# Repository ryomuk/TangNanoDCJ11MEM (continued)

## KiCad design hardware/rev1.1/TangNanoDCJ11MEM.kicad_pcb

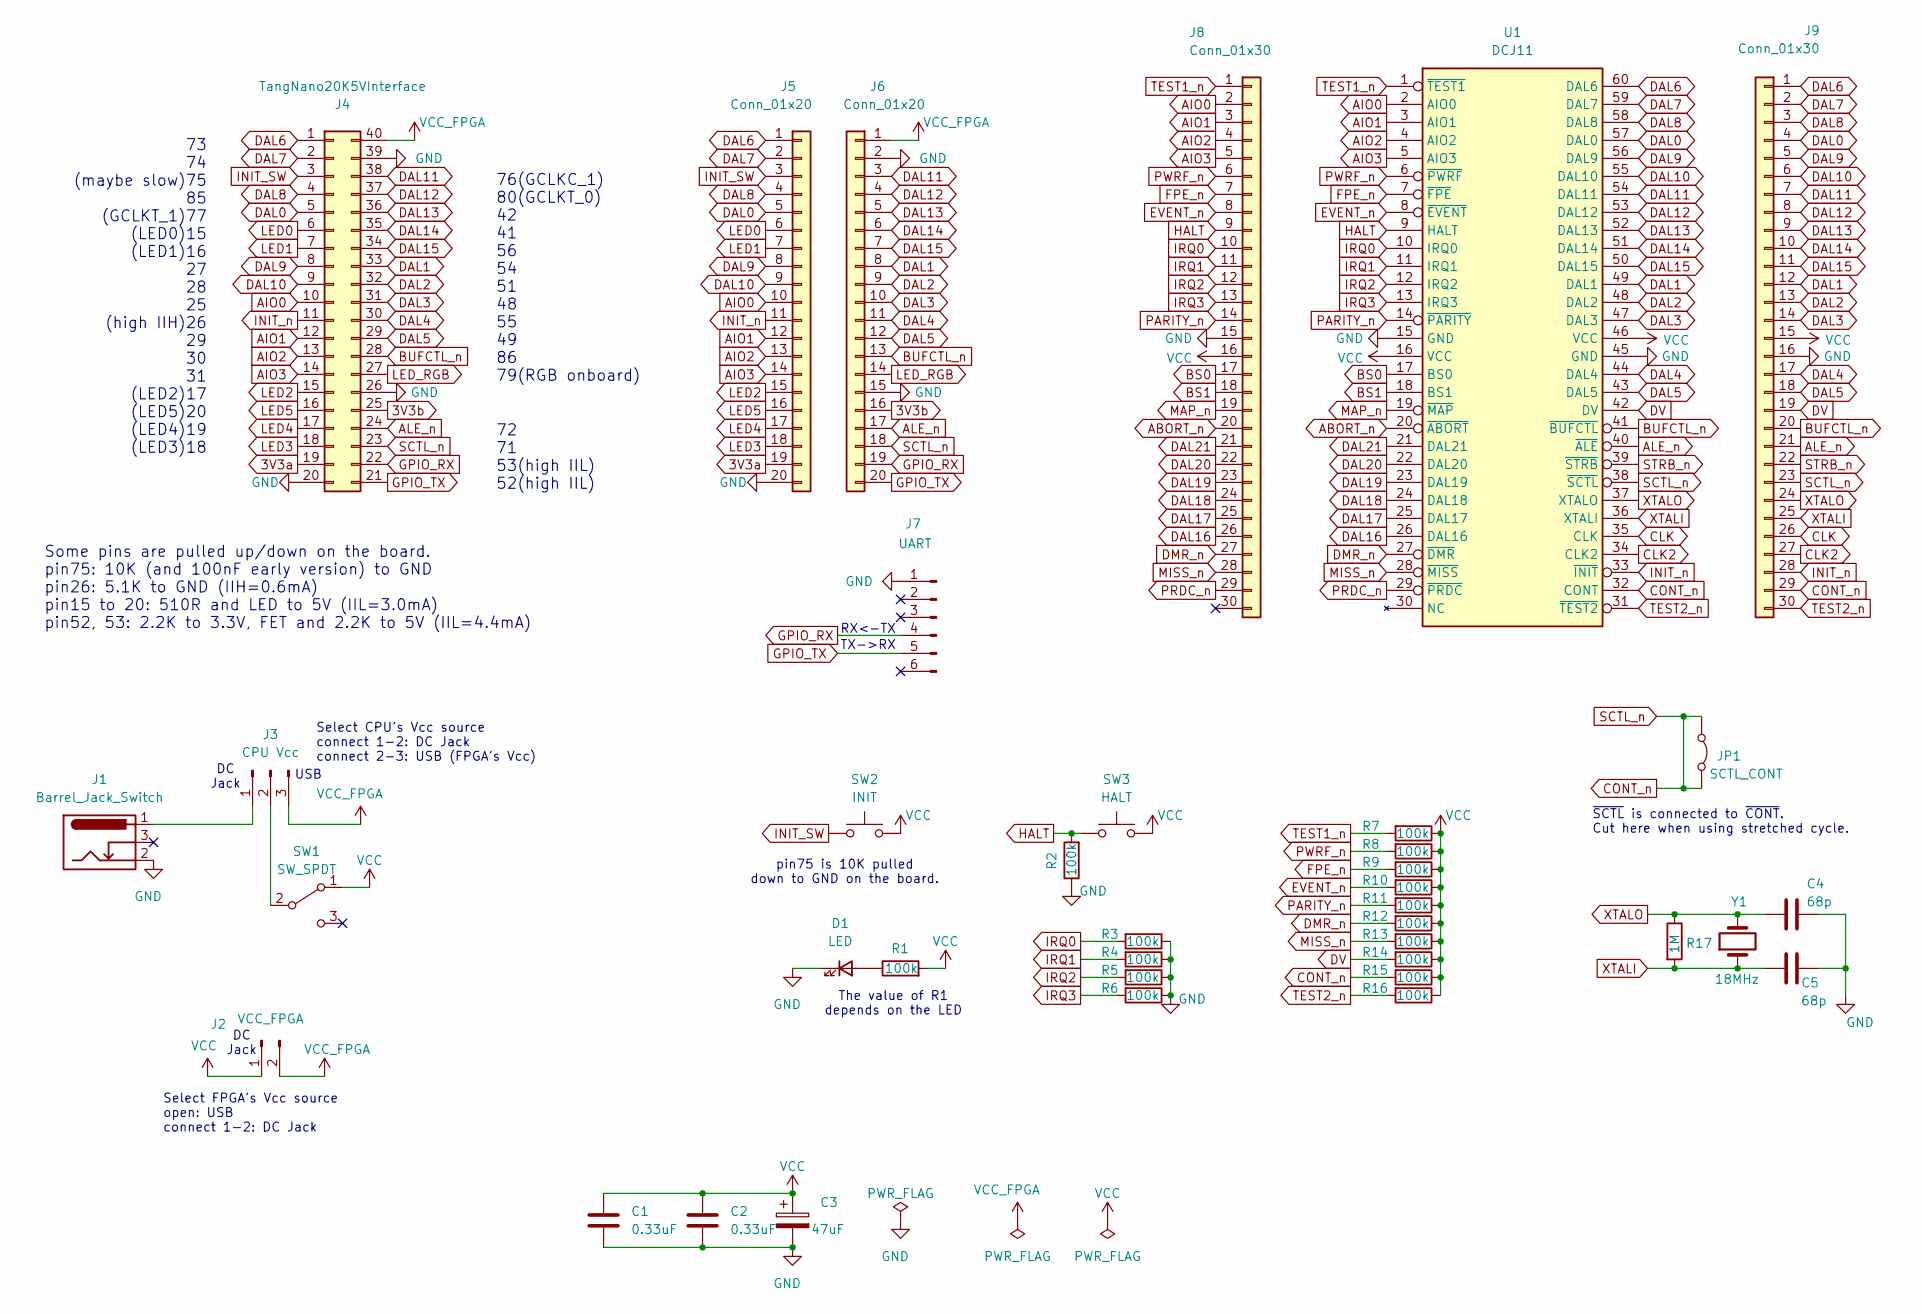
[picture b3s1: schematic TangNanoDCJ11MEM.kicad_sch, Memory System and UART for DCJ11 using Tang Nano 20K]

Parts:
C1, C2: 0.33uF; C_Disc_D5.0mm_W2.5mm_P2.50mm
C3: 47uF; CP_Radial_D6.3mm_P2.50mm
C4, C5: 68p; C_Disc_D5.0mm_W2.5mm_P2.50mm
D1: LED; LED_D3.0mm
J1: Barrel_Jack_Switch; BarrelJack_Horizontal
J2: VCC_FPGA; PinHeader_1x02_P2.54mm_Vertical
J3: CPU Vcc; PinHeader_1x03_P2.54mm_Vertical
J4: TangNano20K5VInterface; DIP-40_W15.24mm_Socket
J5, J6: Conn_01x20; PinSocket_1x20_P2.54mm_Vertical
J7: UART; PinHeader_1x06_P2.54mm_Horizontal
J8, J9: Conn_01x30; PinSocket_1x30_P2.54mm_Vertical
JP1: SCTL_CONT; JumperedPinHeader_1x02_P2.54mm_Vertical
R1, R2, R3, R4, R5, R6, R7, R8, R9, R10, R11, R12, R13, R14, R15, R16: 100k; R_Axial_DIN0207_L6.3mm_D2.5mm_P7.62mm_Horizontal
R17: 1M; R_Axial_DIN0207_L6.3mm_D2.5mm_P7.62mm_Horizontal
SW1: SW_SPDT; SW_SPDT_Toggle_with_mount
SW2: INIT; SW_PUSH_6mm_H4.3mm
SW3: HALT; SW_PUSH_6mm_H4.3mm
U1: DCJ11; DIP-60_W33.02mm_LongPads
Y1: 18MHz; Crystal_HC49-U_Vertical

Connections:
3V3a: J4.19, J5.19
3V3b: J4.25, J6.16
ABORT_n: J8.20, U1.20 (~ABORT)
AIO0: J4.10, J5.10, J8.2, U1.2 (AIO0)
AIO1: J4.12, J5.12, J8.3, U1.3 (AIO1)
AIO2: J4.13, J5.13, J8.4, U1.4 (AIO2)
AIO3: J4.14, J5.14, J8.5, U1.5 (AIO3)
ALE_n: J4.24, J6.17, J9.21, U1.40 (~ALE)
BS0: J8.17, U1.17 (BS0)
BS1: J8.18, U1.18 (BS1)
BUFCTL_n: J4.28, J6.13, J9.20, U1.41 (~BUFCTL)
CLK: J9.26, U1.35 (CLK)
CLK2: J9.27, U1.34 (CLK2)
CONT_n: J4.23, J6.18, J9.23, J9.29, JP1.1 (A), JP1.2 (B), R15.2, U1.32 (CONT), U1.38 (~SCTL)
DAL0: J4.5, J5.5, J9.4, U1.57 (DAL0)
DAL1: J4.33, J6.8, J9.12, U1.49 (DAL1)
DAL2: J4.32, J6.9, J9.13, U1.48 (DAL2)
DAL3: J4.31, J6.10, J9.14, U1.47 (DAL3)
DAL4: J4.30, J6.11, J9.17, U1.44 (DAL4)
DAL5: J4.29, J6.12, J9.18, U1.43 (DAL5)
DAL6: J4.1, J5.1, J9.1, U1.60 (DAL6)
DAL7: J4.2, J5.2, J9.2, U1.59 (DAL7)
DAL8: J4.4, J5.4, J9.3, U1.58 (DAL8)
DAL9: J4.8, J5.8, J9.5, U1.56 (DAL9)
DAL10: J4.9, J5.9, J9.6, U1.55 (DAL10)
DAL11: J4.38, J6.3, J9.7, U1.54 (DAL11)
DAL12: J4.37, J6.4, J9.8, U1.53 (DAL12)
DAL13: J4.36, J6.5, J9.9, U1.52 (DAL13)
DAL14: J4.35, J6.6, J9.10, U1.51 (DAL14)
DAL15: J4.34, J6.7, J9.11, U1.50 (DAL15)
DAL16: J8.26, U1.26 (DAL16)
DAL17: J8.25, U1.25 (DAL17)
DAL18: J8.24, U1.24 (DAL18)
DAL19: J8.23, U1.23 (DAL19)
DAL20: J8.22, U1.22 (DAL20)
DAL21: J8.21, U1.21 (DAL21)
DMR_n: J8.27, R12.2, U1.27 (~DMR)
DV: J9.19, R14.2, U1.42 (DV)
EVENT_n: J8.8, R10.2, U1.8 (~EVENT)
FPE_n: J8.7, R9.2, U1.7 (~FPE)
GND: C1.2, C2.2, C3.2, C4.1, C5.1, D1.1 (K), J1.2, J4.20, J4.26, J4.39, J5.20, J6.2, J6.15, J7.1, J8.15, J9.16, R2.1, R3.1, R4.1, R5.1, R6.1, U1.15 (GND), U1.45 (GND)
GPIO_RX: J4.22, J6.19, J7.4
GPIO_TX: J4.21, J6.20, J7.5
HALT: J8.9, R2.2, SW3.2, U1.9 (HALT)
INIT_SW: J4.3, J5.3, SW2.2
INIT_n: J4.11, J5.11, J9.28, U1.33 (~INIT)
IRQ0: J8.10, R3.2, U1.10 (IRQ0)
IRQ1: J8.11, R4.2, U1.11 (IRQ1)
IRQ2: J8.12, R5.2, U1.12 (IRQ2)
IRQ3: J8.13, R6.2, U1.13 (IRQ3)
LED0: J4.6, J5.6
LED1: J4.7, J5.7
LED2: J4.15, J5.15
LED3: J4.18, J5.18
LED4: J4.17, J5.17
LED5: J4.16, J5.16
LED_RGB: J4.27, J6.14
MAP_n: J8.19, U1.19 (~MAP)
MISS_n: J8.28, R13.2, U1.28 (~MISS)
unnamed: D1.2 (A), R1.1
unnamed: J1.1, J3.1
unnamed: J3.2, SW1.2 (B)
PARITY_n: J8.14, R11.2, U1.14 (~PARITY)
PRDC_n: J8.29, U1.29 (~PRDC)
PWRF_n: J8.6, R8.2, U1.6 (~PWRF)
STRB_n: J9.22, U1.39 (~STRB)
TEST1_n: J8.1, R7.2, U1.1 (~TEST1)
TEST2_n: J9.30, R16.2, U1.31 (~TEST2)
VCC: C1.1, C2.1, C3.1, J2.1, J8.16, J9.15, R1.2, R7.1, R8.1, R9.1, R10.1, R11.1, R12.1, R13.1, R14.1, R15.1, R16.1, SW1.1 (A), SW2.1, SW3.1, U1.16 (VCC), U1.46 (VCC)
VCC_FPGA: J2.2, J3.3, J4.40, J6.1
XTALI: C5.2, J9.25, R17.2, U1.36 (XTALI), Y1.1
XTALO: C4.2, J9.24, R17.1, U1.37 (XTALO), Y1.2

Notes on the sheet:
RX<-TX
USB
72 71 53(high IIL) 52(high IIL)
73 74 (maybe slow)75 85 (GCLKT_1)77 (LED0)15 (LED1)16 27 28 25 (high IIH)26 29 30 31 (LED2)17 (LED5)20 (LED4)19 (LED3)18
76(GCLKC_1) 80(GCLKT_0) 42 41 56 54 51 48 55 49 86 79(RGB onboard)
Some pins are pulled up/down on the board. pin75: 10K (and 100nF early version) to GND pin26: 5.1K to GND (IIH=0.6mA) pin15 to 20: 510R and LED to 5V (IIL=3.0mA) pin52, 53: 2.2K to 3.3V, FET and 2.2K to 5V (IIL=4.4mA)
DC Jack
Select FPGA's Vcc source open: USB connect 1-2: DC Jack
Select CPU's Vcc source connect 1-2: DC Jack connect 2-3: USB (FPGA's Vcc)
The value of R1 depends on the LED
TX->RX
~{SCTL} is connected to ~{CONT}. Cut here when using stretched cycle.
pin75 is 10K pulled down to GND on the board.

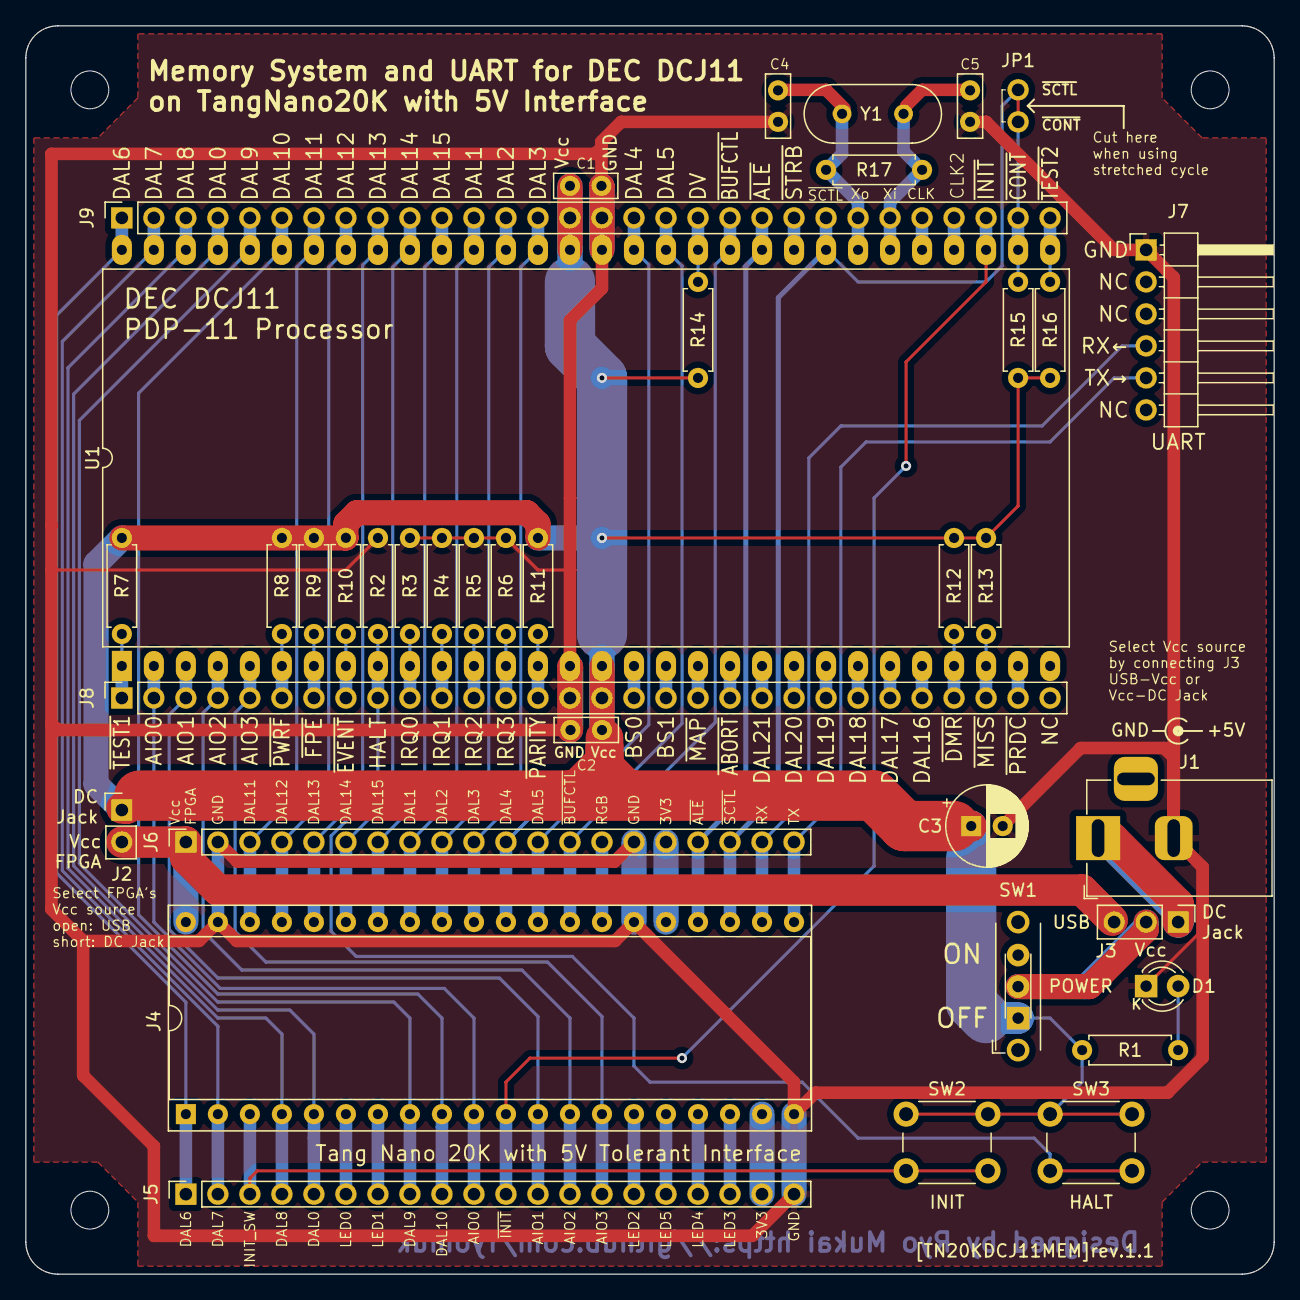
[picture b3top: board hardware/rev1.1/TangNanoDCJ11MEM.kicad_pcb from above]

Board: 2 copper layers, 99.1 x 99.1 mm, 38 parts (0 on the bottom side), 72 nets.

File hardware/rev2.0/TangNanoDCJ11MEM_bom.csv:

Reference,Value,Datasheet,Footprint,Qty,DNP
"C1,C2",0.33uF,~,000_MyFootprint:C_Disc_D5.0mm_W2.5mm_P2.50mm,2,
C3,47uF,~,000_MyFootprint:CP_Radial_D6.3mm_P2.50mm,1,
"C4,C5",68p,~,000_MyFootprint:C_Disc_D5.0mm_W2.5mm_P2.50mm,2,
D1,LED,~,000_MyFootprint:LED_D3.0mm,1,
J1,Barrel_Jack_Switch,~,000_MyFootprint:BarrelJack_Horizontal,1,
J2,VCC_FPGA,~,000_MyFootprint:PinHeader_1x02_P2.54mm_Vertical,1,
J3,CPU Vcc,~,000_MyFootprint:PinHeader_1x03_P2.54mm_Vertical,1,
J4,TangNano20K5VInterface,~,000_MyFootprint:DIP-40_W15.24mm_Socket,1,
"J5,J6",Conn_01x20,~,000_MyFootprint:PinSocket_1x20_P2.54mm_Vertical,2,
J7,UART,~,000_MyFootprint:PinHeader_1x06_P2.54mm_Horizontal,1,
"J8,J9",Conn_01x30,~,000_MyFootprint:PinSocket_1x30_P2.54mm_Vertical,2,
JP1,SCTL_CONT,~,000_MyFootprint:JumperedPinHeader_1x02_P2.54mm_Vertical,1,
"R1,R7,R8,R9,R10,R11,R12,R13,R14,R15,R16",100k,~,000_MyFootprint:R_Axial_DIN0207_L6.3mm_D2.5mm_P7.62mm_Horizontal,11,
"R2,R3,R4,R5,R6",10k,,000_MyFootprint:R_Axial_DIN0207_L6.3mm_D2.5mm_P7.62mm_Horizontal,5,
R17,1M,~,000_MyFootprint:R_Axial_DIN0207_L6.3mm_D2.5mm_P7.62mm_Horizontal,1,
SW1,SW_SPDT,~,000_MyFootprint:SW_SPDT_Toggle_with_mount,1,
SW2,INIT,~,000_MyFootprint:SW_PUSH_6mm_H4.3mm,1,
SW3,HALT,~,000_MyFootprint:SW_PUSH_6mm_H4.3mm,1,
U1,DCJ11,,000_MyFootprint:DIP-60_W33.02mm_LongPads,1,
Y1,18MHz,~,000_MyFootprint:Crystal_HC49-U_Vertical,1,

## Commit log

2024-05-22 papertape emulator updated
2024-05-22 README updated
2024-06-18 sdtape.v bugfixed
2024-06-24 unixv1 initial commit
2024-06-28 tapebasic updated
2024-06-28 0628.alpha updated
2024-07-02 0702.alpha updated
2024-07-03 0703.alpha uploaded
2024-07-04 0704.alpha uploaded
2024-07-07 baremetal updated
2024-07-07 20240707.alpha uploaded
2024-07-09 20240709.alpha uploaded
2024-07-10 20240710.alpha uploaded
2024-07-12 20240712.alpha uploaded
2024-07-13 20240713.alpha uploaded
2024-07-14 20240714.alpha uploaded
2024-07-15 R2-6 changed
2024-07-16 20240716.beta uploaded
2024-07-19 20240719.beta uploaded
2024-07-26 20240726.beta uploaded
2024-07-26 20240726.beta cancelled
2024-07-27 20240727.beta updated
2024-07-28 20240728.beta uploaded
2024-07-29 update for unix v6
2024-07-29 20240729.beta uploaded
2024-07-29 20240730.v6.beta uploaded
2024-07-30 20240730a.v6.beta uploaded
2025-09-03 README.md updated
2025-09-04 update for PCB rev2
2025-09-05 PCB rev2.1 released
2025-09-05 PCB rev2.2 released
2025-09-15 code for rev2 updated
2025-09-17 20250917.pcbrev2 released
2025-09-17 REAMDE updated
2025-09-22 major update
2025-09-22 pcb rev3.1 released
2025-09-26 impl folders removed
2025-09-26 gitignore added
2025-09-29 HDL for RT11 released
